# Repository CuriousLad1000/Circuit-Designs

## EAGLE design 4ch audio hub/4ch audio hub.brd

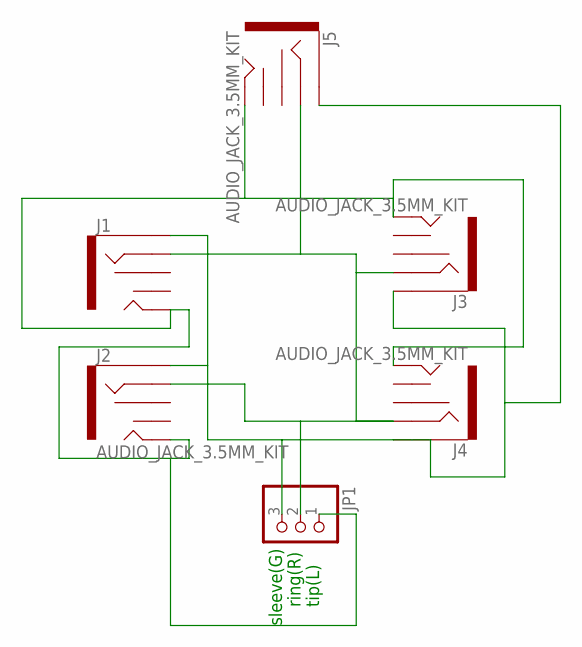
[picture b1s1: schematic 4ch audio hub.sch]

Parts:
J1: ring; AUDIO-JACK-KIT
J2, J3, J4, J5: AUDIO_JACK_3.5MM_KIT; AUDIO-JACK-KIT
JP1: PINHD-1X3; 1X03

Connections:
unnamed: J1.SLEEVE, J2.SLEEVE, J3.SLEEVE, J4.SLEEVE, J5.SLEEVE, JP1.3
unnamed: J1.RING, J2.RING, J3.RING, J4.RING, J5.RING, JP1.2
unnamed: J1.TIP, J2.TIP, J3.TIP, J4.TIP, J5.TIP, JP1.1

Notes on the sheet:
ring(R)
sleeve(G)
tip(L)

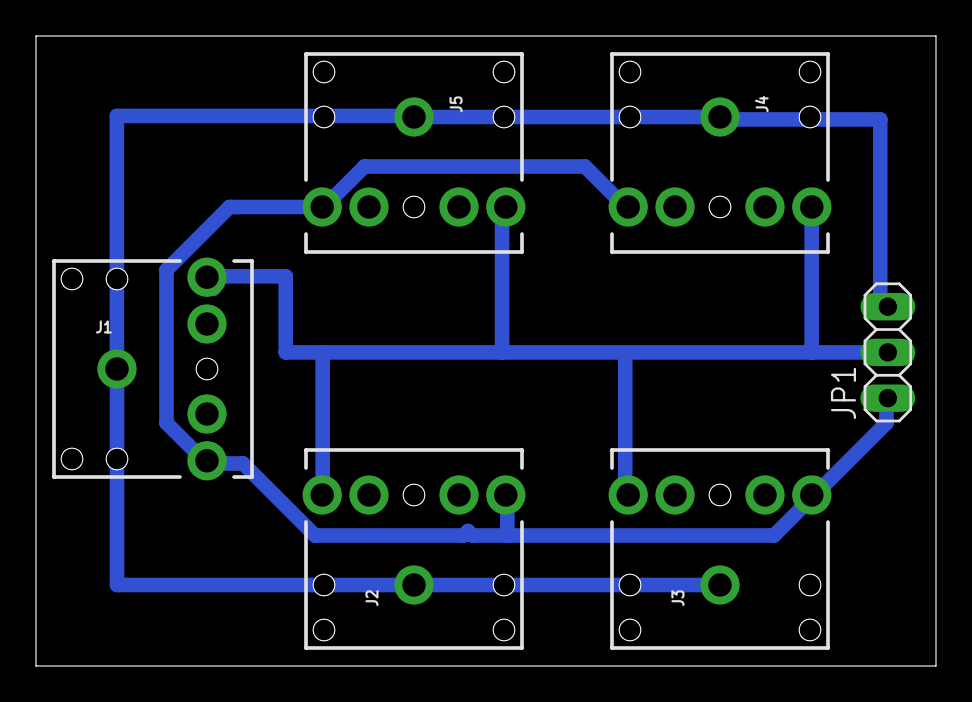
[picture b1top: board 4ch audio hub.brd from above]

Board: 2 copper layers, 50.0 x 35.0 mm, 6 parts (0 on the bottom side), 3 nets.

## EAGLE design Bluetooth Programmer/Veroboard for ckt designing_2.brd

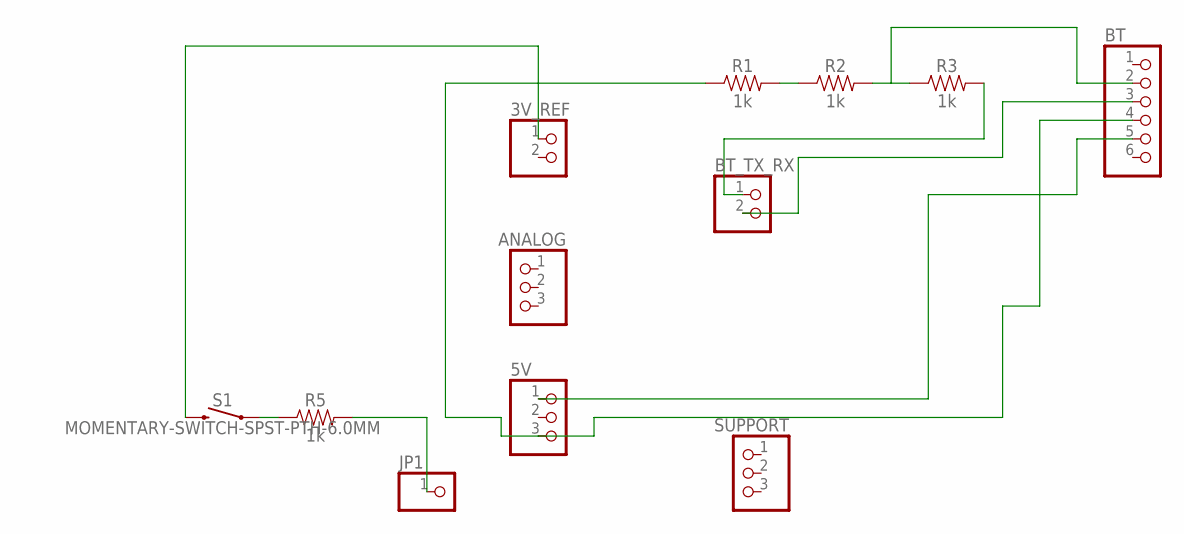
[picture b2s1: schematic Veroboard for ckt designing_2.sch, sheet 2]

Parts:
3V_REF: PINHD-1X2; 1X02
5V: PINHD-1X3; 1X03
ANALOG: PINHD-1X3; 1X03
BT: PINHD-1X6; 1X06
BT_TX_RX: PINHD-1X2; 1X02
JP1: PINHD-1X1; 1X01
R1, R2, R3, R5: 1k; AXIAL-0.3
S1: MOMENTARY-SWITCH-SPST-PTH-6.0MM; TACTILE_SWITCH_PTH_6.0MM
SUPPORT: PINHD-1X3; 1X03

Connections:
3V: 3V_REF.1, S1.3 (2)
5V: 5V.1, BT.5
BT_TX: BT.3, BT_TX_RX.2
G: 5V.3, BT.4, R1.P$1 (1)
unnamed: R1.P$2 (2), R2.P$1 (1)
unnamed: BT.2, R2.P$2 (2), R3.P$1 (1)
unnamed: R5.P$1 (1), S1.1
unnamed: JP1.1, R5.P$2 (2)
RX: BT_TX_RX.1, R3.P$2 (2)

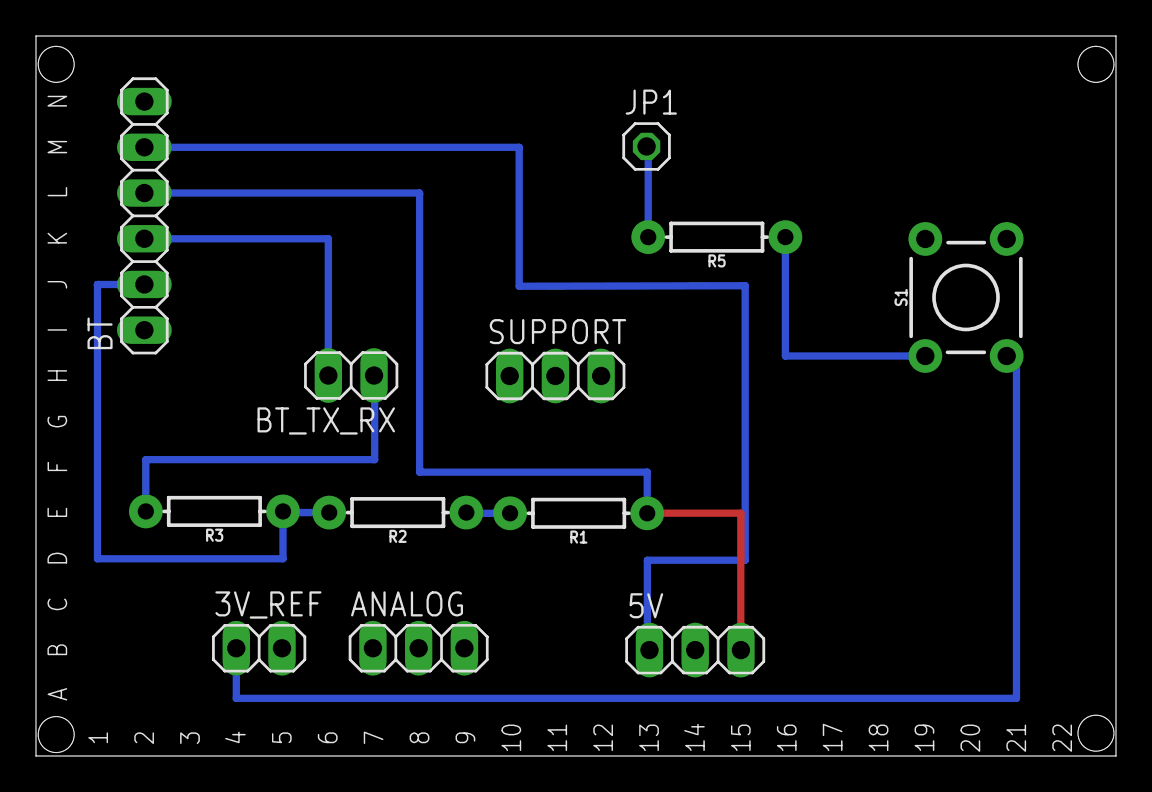
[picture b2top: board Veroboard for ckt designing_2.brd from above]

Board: 2 copper layers, 60.0 x 40.0 mm, 34 parts (0 on the bottom side), 9 nets.

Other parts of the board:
U$1, U$2, U$3, U$4, U$5, U$6, U$7, U$8, U$9, U$10, U$11, U$12, U$13, U$14, U$15, U$16, U$17, U$18, U$19, U$20, U$21, U$22: 1X14

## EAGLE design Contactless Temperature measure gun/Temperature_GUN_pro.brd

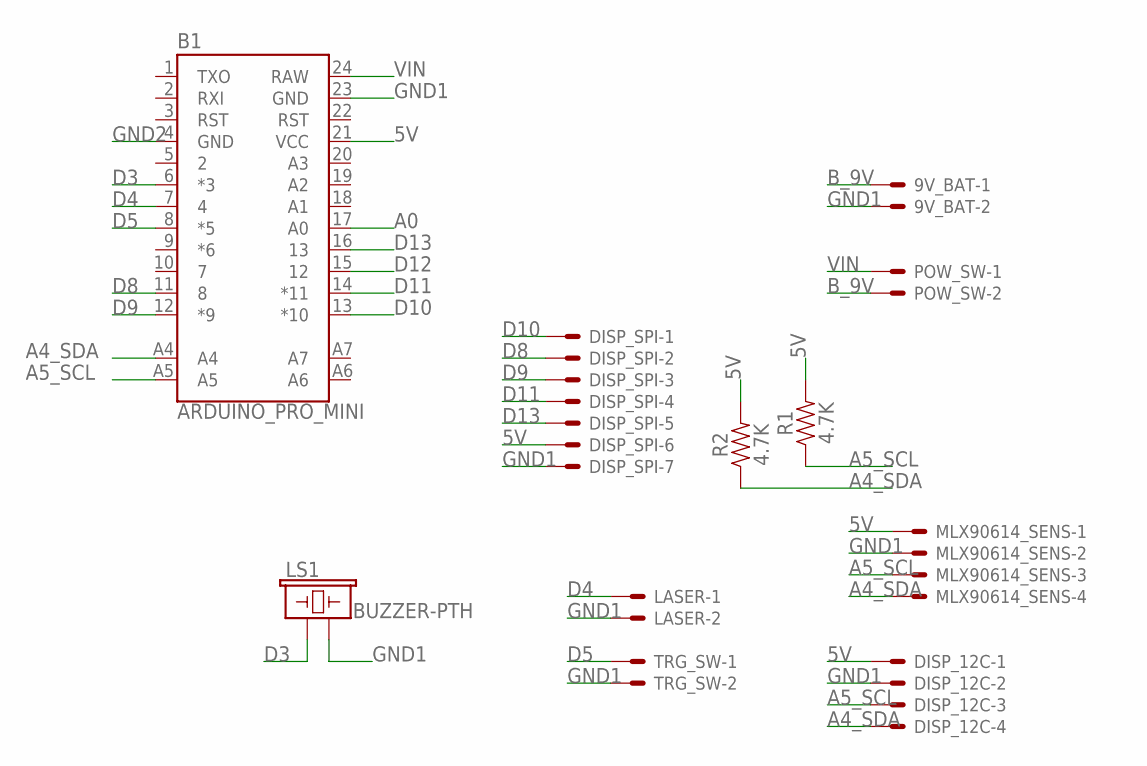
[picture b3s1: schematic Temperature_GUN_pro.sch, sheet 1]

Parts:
9V_BAT: JST-XH-02-PIN-ROUND-PAD; JST-XH-02-PACKAGE-ROUND-PAD
B1: ARDUINO_PRO_MINI
DISP_12C: JST-XH-04-PIN-ROUND-PAD; JST-XH-04-PACKAGE-ROUND-PAD
DISP_SPI: JST-XH-07-PIN-ROUND-PAD; JST-XH-07-PACKAGE-ROUND-PAD
LASER: JST-XH-02-PIN-ROUND-PAD; JST-XH-02-PACKAGE-ROUND-PAD
LS1: BUZZER-PTH; BUZZER-12MM
MLX90614_SENS: JST-XH-04-PIN-ROUND-PAD; JST-XH-04-PACKAGE-ROUND-PAD
POW_SW: JST-XH-02-PIN-ROUND-PAD; JST-XH-02-PACKAGE-ROUND-PAD
R1, R2: 4.7K; AXIAL-0.3
TRG_SW: JST-XH-02-PIN-ROUND-PAD; JST-XH-02-PACKAGE-ROUND-PAD

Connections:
5V: B1.21 (VCC), DISP_12C.1, DISP_SPI.6, MLX90614_SENS.1, R1.P$2 (2), R2.P$2 (2)
A0: B1.17 (A0)
A4_SDA: B1.A4, DISP_12C.4, MLX90614_SENS.4, R2.P$1 (1)
A5_SCL: B1.A5, DISP_12C.3, MLX90614_SENS.3, R1.P$1 (1)
B_9V: 9V_BAT.1, POW_SW.2
D3: B1.6 (*3), LS1.+ (1)
D4: B1.7 (4), LASER.1
D5: B1.8 (*5), TRG_SW.1
D8: B1.11 (8), DISP_SPI.2
D9: B1.12 (*9), DISP_SPI.3
D10: B1.13 (*10), DISP_SPI.1
D11: B1.14 (*11), DISP_SPI.4
D12: B1.15 (12)
D13: B1.16 (13), DISP_SPI.5
GND1: 9V_BAT.2, B1.23 (GND), DISP_12C.2, DISP_SPI.7, LASER.2, LS1.- (2), MLX90614_SENS.2, TRG_SW.2
GND2: B1.4 (GND)
VIN: B1.24 (RAW), POW_SW.1

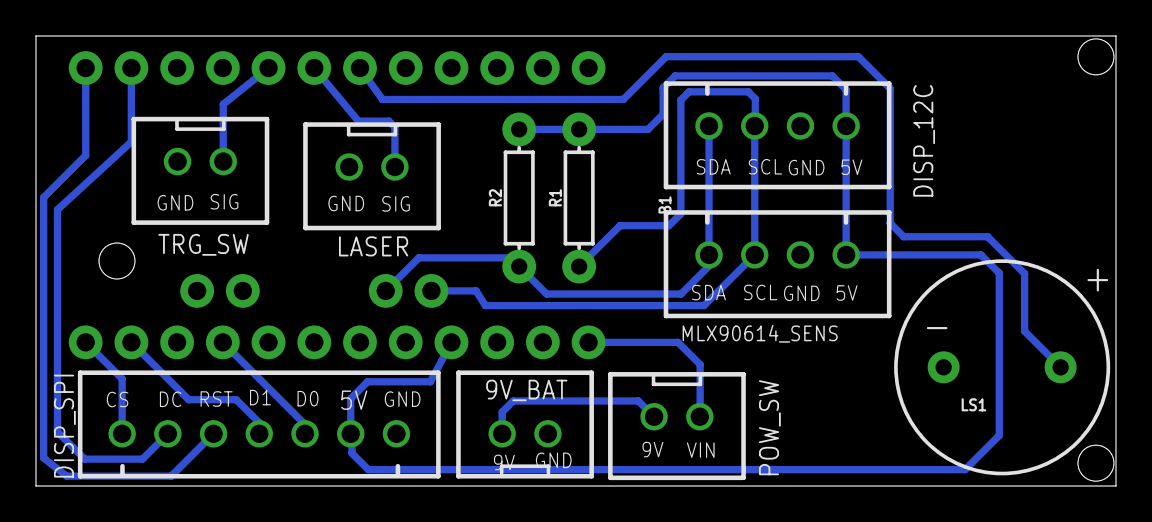
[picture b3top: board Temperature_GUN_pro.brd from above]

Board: 2 copper layers, 60.0 x 25.0 mm, 11 parts (0 on the bottom side), 14 nets.

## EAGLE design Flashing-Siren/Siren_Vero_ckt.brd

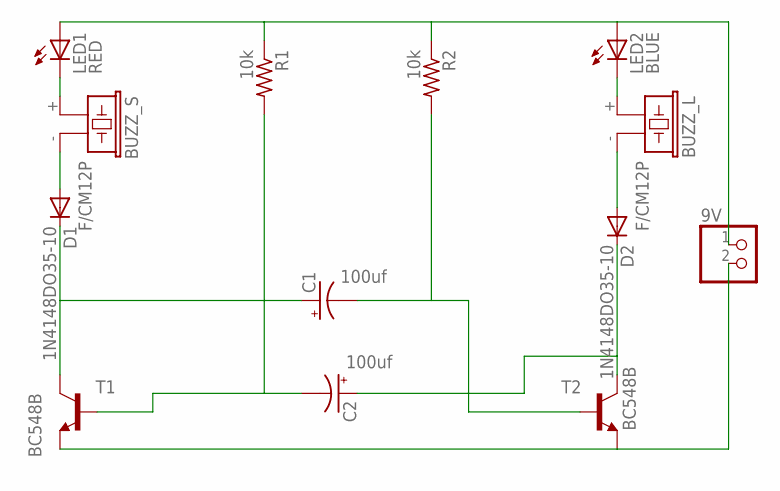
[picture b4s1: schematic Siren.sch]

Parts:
9V: PINHD-1X2; 1X02
BUZZ_L: F/CM12P
BUZZ_S: F/CM12P
C1, C2: 100uf; E2,5-5
D1, D2: 1N4148DO35-10; DO35-10
LED1: RED; LED5MM
LED2: BLUE; LED5MM
R1, R2: 10k; 0204/7
T1, T2: BC548B; TO92-CBE

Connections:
unnamed: BUZZ_S.+ (1), LED1.K (C)
unnamed: BUZZ_S.- (2), D1.A
unnamed: C1.+, D1.C, T1.C
unnamed: 9V.2, T1.E, T2.E
unnamed: BUZZ_L.+ (1), LED2.K (C)
unnamed: BUZZ_L.- (2), D2.A
unnamed: C2.+, D2.C, T2.C
unnamed: C2.-, R1.2, T1.B
unnamed: C1.-, R2.2, T2.B
unnamed: 9V.1, LED1.A, LED2.A, R1.1, R2.1

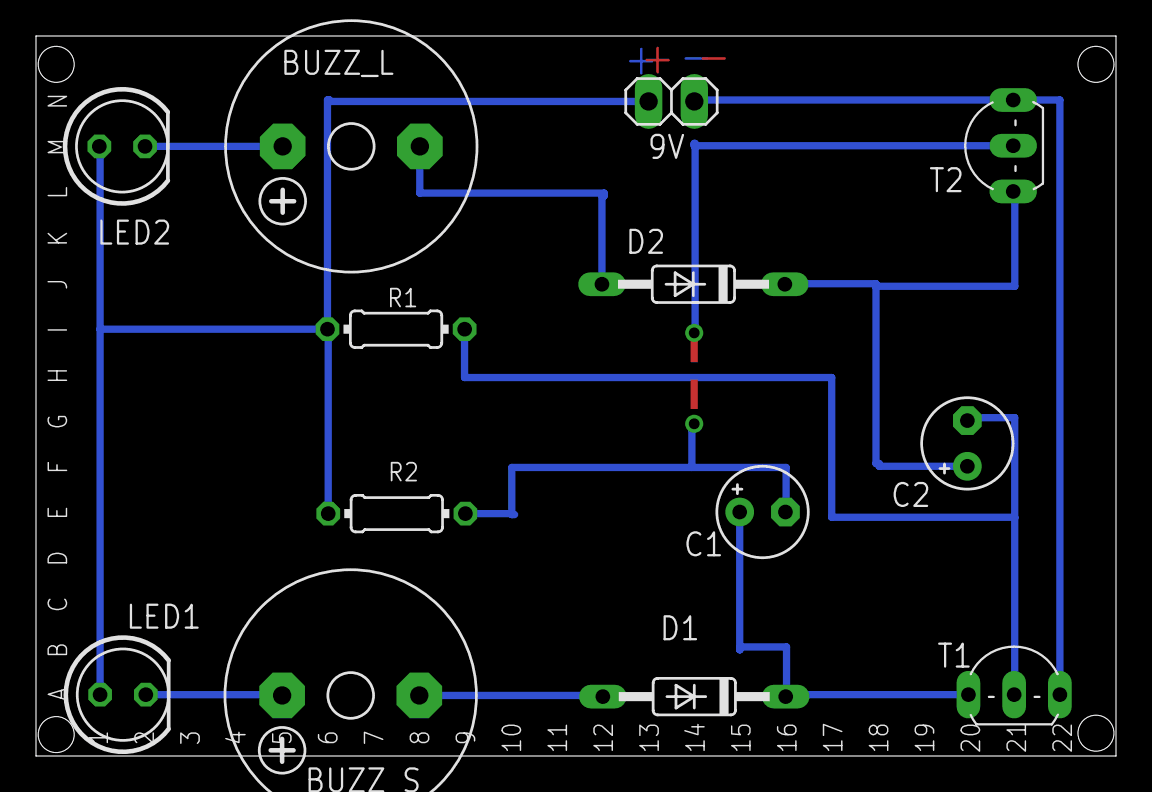
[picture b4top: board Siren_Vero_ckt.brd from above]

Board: 2 copper layers, 60.0 x 40.0 mm, 35 parts (0 on the bottom side), 10 nets.

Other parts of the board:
1, 2, 4: 1X14
JP3, JP5, JP6, JP7, JP8, JP9, JP10, JP11, JP12, JP13, JP14, JP15, JP16, JP17, JP18, JP19, JP20, JP21, JP22: 1X14

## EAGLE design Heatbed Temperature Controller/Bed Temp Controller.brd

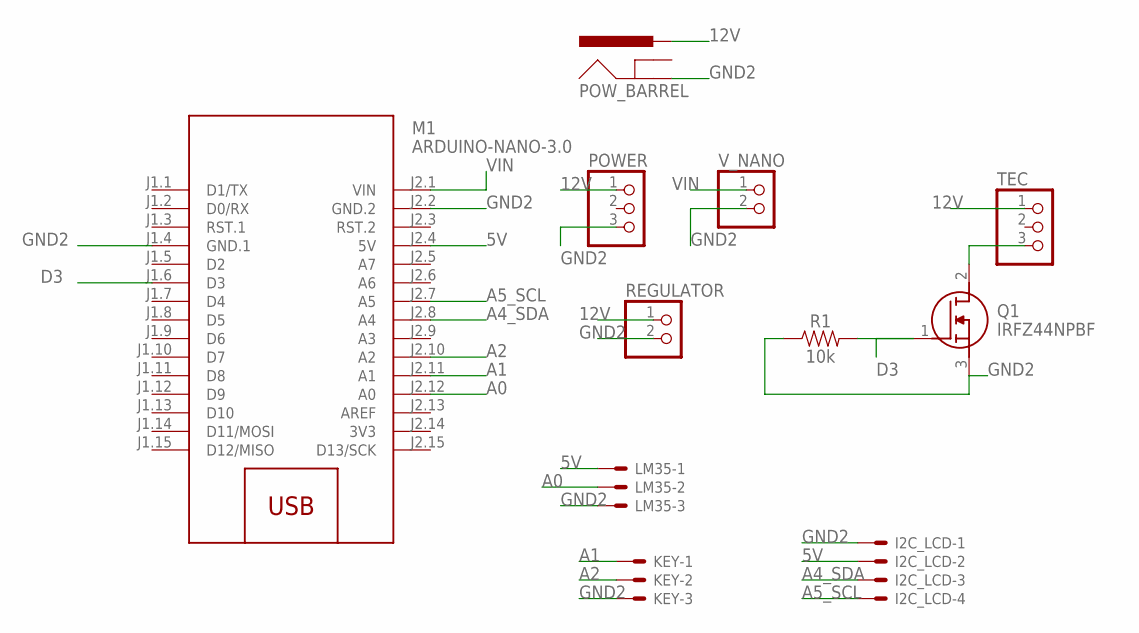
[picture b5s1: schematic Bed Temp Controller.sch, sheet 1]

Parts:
I2C_LCD: JST-XH-04-PIN-ROUND-PAD; JST-XH-04-PACKAGE-ROUND-PAD
KEY: JST-XH-03-PIN-ROUND-PAD; JST-XH-03-PACKAGE-ROUND-PAD
LM35: JST-XH-03-PIN-ROUND-PAD; JST-XH-03-PACKAGE-ROUND-PAD
M1: ARDUINO-NANO-3.0
POWER: PINHD-1X3; 1X03
POW_BARREL: POWER_JACKPTH_BREAD; POWER_JACK_PTH_BREAD
Q1: IRFZ44NPBF; TO254P483X1016X1994-3P
R1: 10k; AXIAL-0.3
REGULATOR: PINHD-1X2; 1X02
TEC: PINHD-1X3; 1X03
V_NANO: PINHD-1X2; 1X02

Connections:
3V3: M1.J2.14 (3V3)
5V: I2C_LCD.2, LM35.1, M1.J2.4 (5V)
12V: POWER.1, POW_BARREL.PWR, REGULATOR.1, TEC.1
A0: LM35.2, M1.J2.12 (A0)
A1: KEY.1, M1.J2.11 (A1)
A2: KEY.2, M1.J2.10 (A2)
A4_SDA: I2C_LCD.3, M1.J2.8 (A4)
A5_SCL: I2C_LCD.4, M1.J2.7 (A5)
D3: M1.J1.6 (D3), Q1.1 (G), R1.P$2 (2)
D-TEC: Q1.2 (D), TEC.3
GND2: I2C_LCD.1, KEY.3, LM35.3, M1.J1.4 (GND.1), M1.J2.2 (GND.2), POWER.3, POW_BARREL.GND, Q1.3 (S), R1.P$1 (1), REGULATOR.2, V_NANO.2
VIN: M1.J2.1 (VIN), V_NANO.1

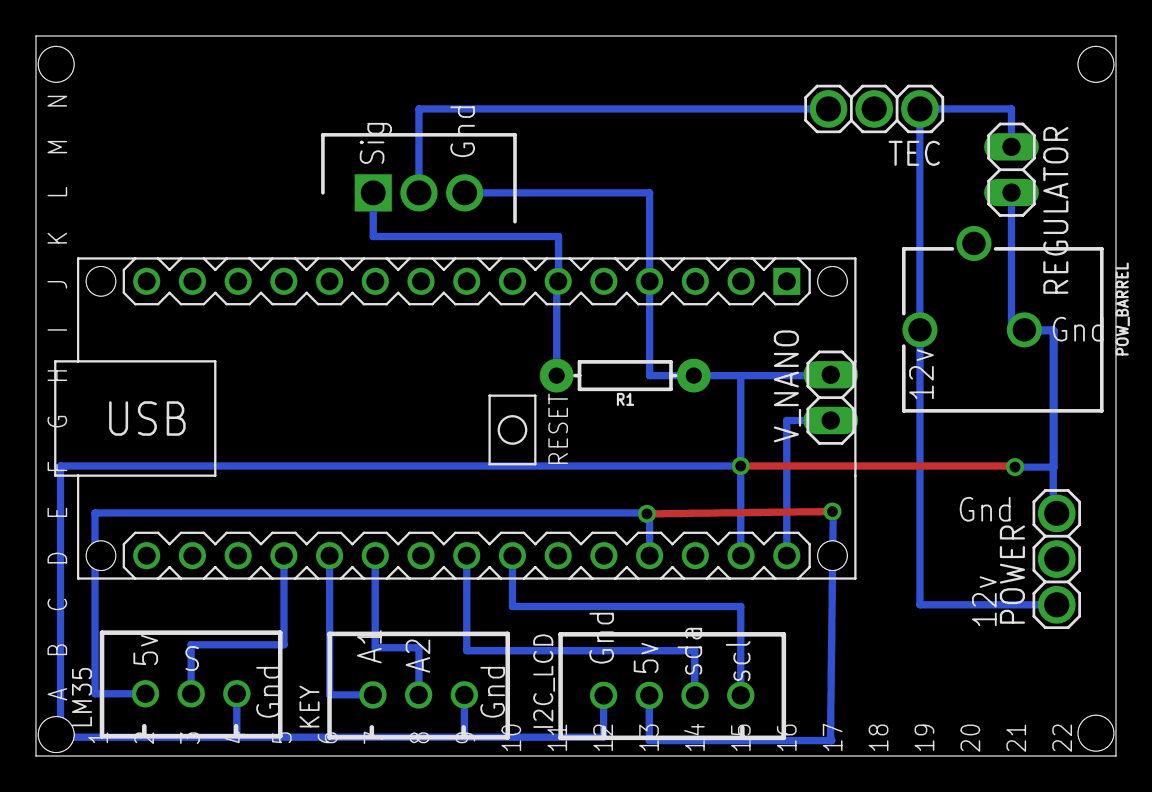
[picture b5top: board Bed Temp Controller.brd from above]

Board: 2 copper layers, 60.0 x 40.0 mm, 33 parts (0 on the bottom side), 11 nets.

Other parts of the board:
U$1, U$2, U$3, U$4, U$5, U$6, U$7, U$8, U$9, U$10, U$11, U$12, U$13, U$14, U$15, U$16, U$17, U$18, U$19, U$20, U$21, U$22: 1X14

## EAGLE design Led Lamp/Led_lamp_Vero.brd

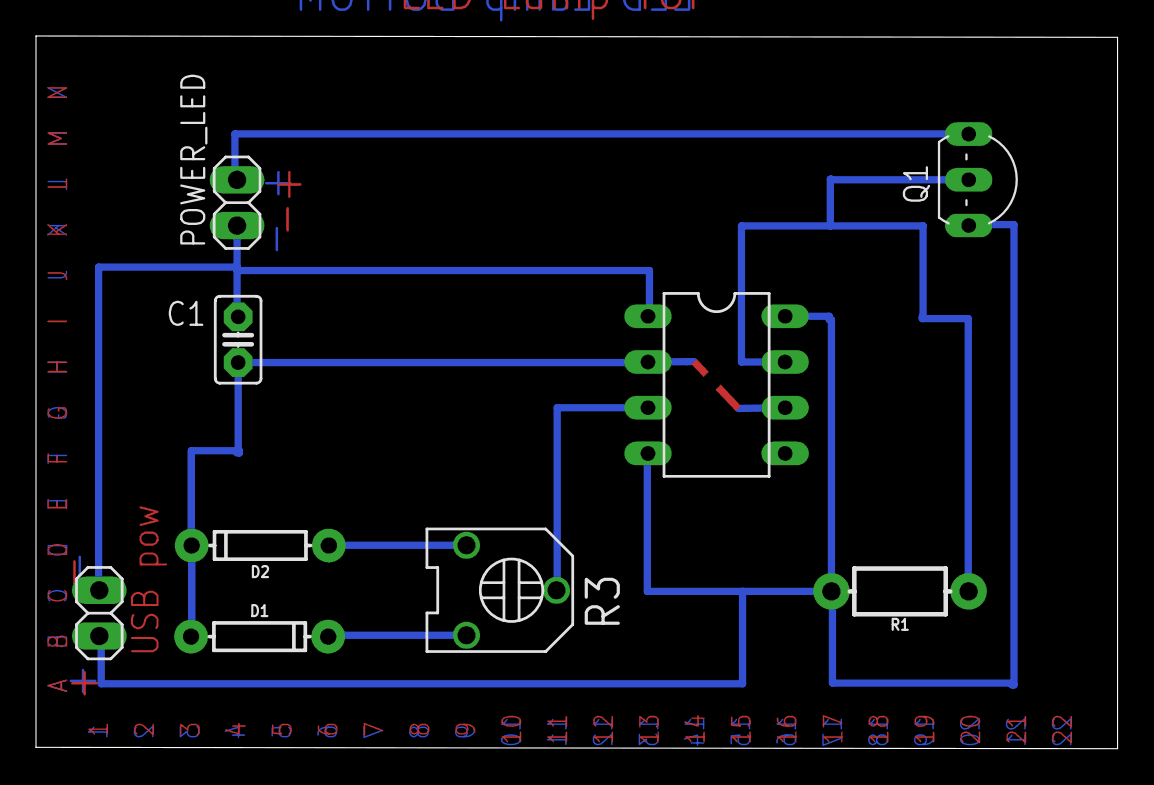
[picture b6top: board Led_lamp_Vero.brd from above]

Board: 2 copper layers, 60.1 x 39.6 mm, 31 parts (0 on the bottom side), 8 nets.

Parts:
1, 2, 4: 1X14
C1: 0.1uf; C0.1PTH
D1, D2: 1N4148; DIODE-1N4148
IC1: NE555; DIL-08
JP1: 1X02
JP3, JP5, JP6, JP7, JP8, JP9, JP10, JP11, JP12, JP13, JP14, JP15, JP16, JP17, JP18, JP19, JP20, JP21, JP22: 1X14
POWER_LED: 1X02
Q1: 2N2222; TO92-EBC
R1: 4.7k; AXIAL-0.3-KIT
R3: 10k; TRIMMER_3306F

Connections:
GND: C1.2, IC1.1, JP1.2, POWER_LED.1
unnamed: IC1.7, Q1.B, R1.P$1
unnamed: C1.1, D1.A, D2.C, IC1.2, IC1.6
unnamed: D1.C, R3.3
unnamed: D2.A, R3.1
unnamed: IC1.3, R3.2
unnamed: POWER_LED.2, Q1.E
VCC: IC1.4, IC1.8, JP1.1, Q1.C, R1.P$2

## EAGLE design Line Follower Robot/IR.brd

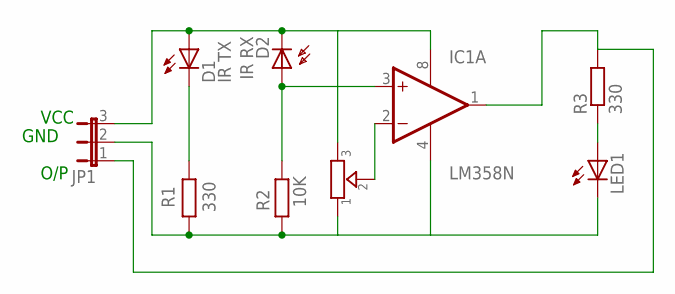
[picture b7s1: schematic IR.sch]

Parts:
D1: IR TX; SFH482
D2: IR RX; BPW32
IC1: LM358N; DIL08
JP1: JP2E; JP2
LED1: LEDLZR181; LZR181
R1, R3: 330; 0204/7
R2: 10K; 0204/7
R5: TRIMMER-3306F; TRIMMER_3306F

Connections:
unnamed: D1.A, D2.K (C), IC1.8 (V+), JP1.3, R5.3
unnamed: D1.K (C), R1.2
unnamed: IC1.4 (V-), JP1.2, LED1.K (C), R1.1, R2.1, R5.1
unnamed: LED1.A, R3.1
unnamed: IC1.1 (OUT), JP1.1, R3.2
unnamed: IC1.2 (-IN), R5.2
unnamed: D2.A, IC1.3 (+IN), R2.2

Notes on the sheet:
VCC
GND
O/P

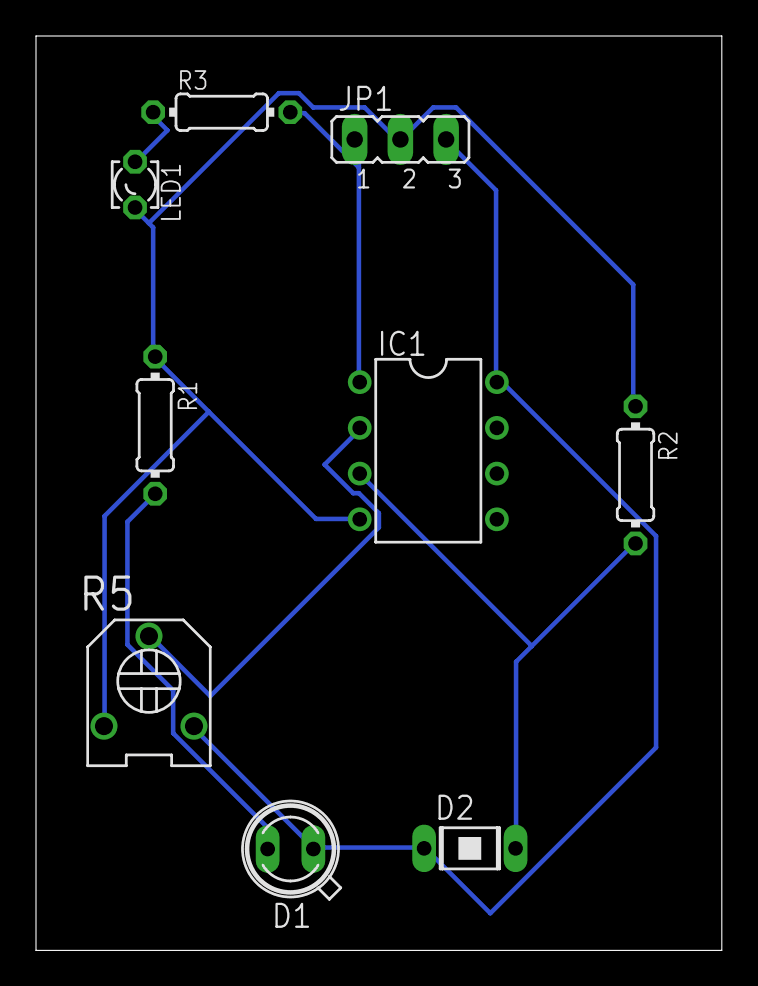
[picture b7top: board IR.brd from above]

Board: 2 copper layers, 38.1 x 50.8 mm, 9 parts (0 on the bottom side), 7 nets.

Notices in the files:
parts and their libraries:
SparkFun-Connectors: Licensing: Creative Commons ShareAlike 4.0 International - https://creativecommons.org/licenses/by-sa/4.0
diy-modules: Released under the Creative Commons Attribution 4.0 International License: http://creativecommons.org/licenses/by/4.0
